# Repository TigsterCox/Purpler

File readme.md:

This is my first keyboard i've ever made
I do NOT reccomend you attempt building it
the current QMK firmware is built for the *BODGED* PCB whereas the KiCad files are for a *FIXED* PCB though it shouldnt be too hard of a fix

Its a 71 Key QWERTY UK ISO build based off of the Durgod Hades 69 ISO
my build uses AKKO Lavender Purple V3's and a generic keycap set from aliex
The RP2040 is a WEACT rpi 2040 as it is also purple (i think you get the theme here)
I use m2x6mm screws that are threaded into plastic, tho you can also adjust it for heatsets and shorter screws (which i plan on doing if i ever do a rebuild)

AGAIN, I DO NOT RECCOMEND BUILDING THIS

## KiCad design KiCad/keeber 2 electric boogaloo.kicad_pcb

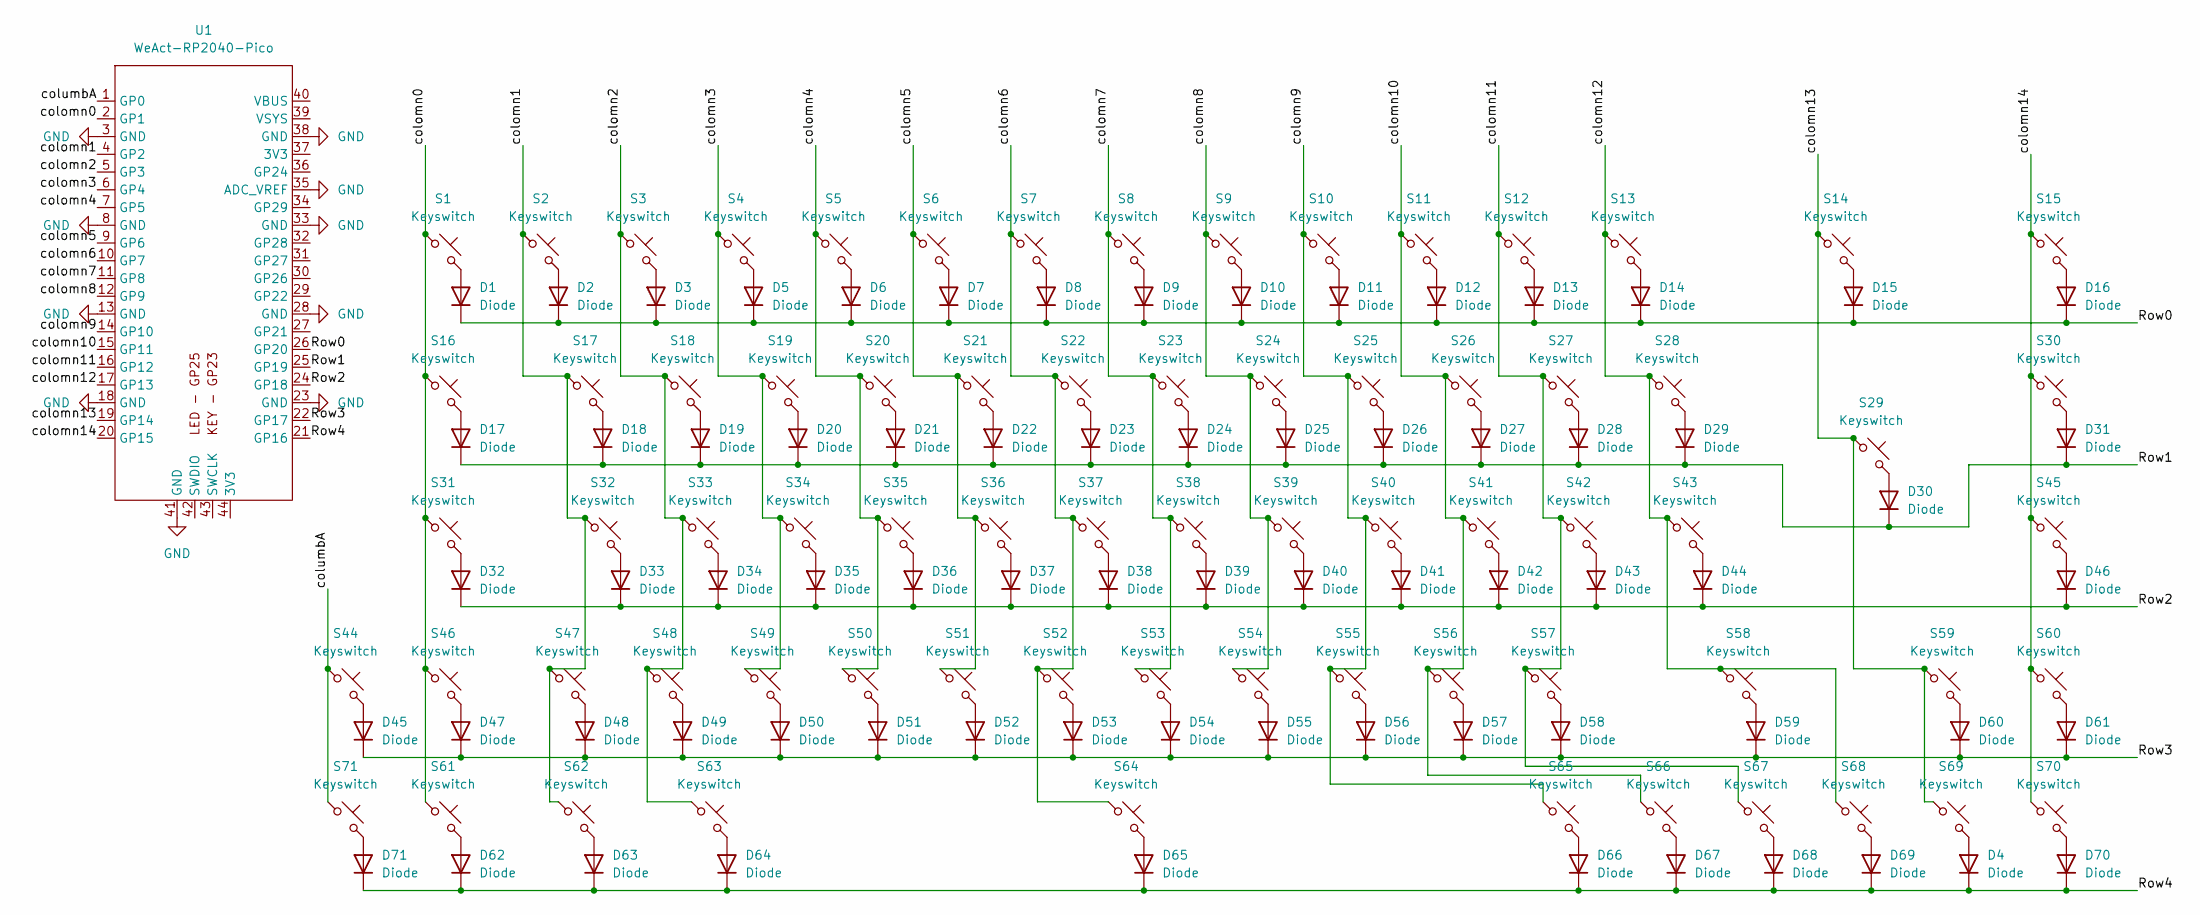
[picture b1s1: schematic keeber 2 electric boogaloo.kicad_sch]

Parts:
D1, D2, D3, D4, D5, D6, D7, D8, D9, D10, D11, D12, D13, D14, D15, D16, D17, D18, D19, D20, D21, D22, D23, D24, D25, D26, D27, D28, D29, D30, D31, D32, D33, D34, D35, D36, D37, D38, D39, D40, D41, D42, D43, D44, D45, D46, D47, D48, D49, D50, D51, D52, D53, D54, D55, D56, D57, D58, D59, D60, D61, D62, D63, D64, D65, D66, D67, D68, D69, D70, D71: Diode; D_SOD-123
S1, S2, S3, S4, S5, S6, S7, S8, S9, S10, S11, S12, S13, S15, S17, S18, S19, S20, S21, S22, S23, S24, S25, S26, S27, S28, S30, S32, S33, S34, S35, S36, S37, S38, S39, S40, S41, S42, S43, S45, S47, S48, S49, S50, S51, S52, S53, S54, S55, S56, S57, S59, S60, S65, S66, S67, S68, S69, S70: Keyswitch; Hotswap_MX_1.00u
S14: Keyswitch; Hotswap_MX_2.00u
S16, S44, S71: Keyswitch; Hotswap_MX_1.50u
S29: Keyswitch; Hotswap_MX_ISOEnter
S31, S58: Keyswitch; Hotswap_MX_1.75u
S46, S61, S62, S63: Keyswitch; Hotswap_MX_1.25u
S64: Keyswitch; Hotswap_MX_6.25u
U1: WeAct-RP2040-Pico

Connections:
/Row0: D1.1 (K), D2.1 (K), D3.1 (K), D5.1 (K), D6.1 (K), D7.1 (K), D8.1 (K), D9.1 (K), D10.1 (K), D11.1 (K), D12.1 (K), D13.1 (K), D14.1 (K), D15.1 (K), D16.1 (K), U1.26 (GP20)
/Row1: D17.1 (K), D18.1 (K), D19.1 (K), D20.1 (K), D21.1 (K), D22.1 (K), D23.1 (K), D24.1 (K), D25.1 (K), D26.1 (K), D27.1 (K), D28.1 (K), D29.1 (K), D30.1 (K), D31.1 (K), U1.25 (GP19)
/Row2: D32.1 (K), D33.1 (K), D34.1 (K), D35.1 (K), D36.1 (K), D37.1 (K), D38.1 (K), D39.1 (K), D40.1 (K), D41.1 (K), D42.1 (K), D43.1 (K), D44.1 (K), D46.1 (K), U1.24 (GP18)
/Row3: D45.1 (K), D47.1 (K), D48.1 (K), D49.1 (K), D50.1 (K), D51.1 (K), D52.1 (K), D53.1 (K), D54.1 (K), D55.1 (K), D56.1 (K), D57.1 (K), D58.1 (K), D59.1 (K), D60.1 (K), D61.1 (K), U1.22 (GP17)
/Row4: D4.1 (K), D62.1 (K), D63.1 (K), D64.1 (K), D65.1 (K), D66.1 (K), D67.1 (K), D68.1 (K), D69.1 (K), D70.1 (K), D71.1 (K), U1.21 (GP16)
/colomn0: S1.1, S16.1, S31.1, S46.1, S61.1, U1.2 (GP1)
/colomn1: S2.1, S17.1, S32.1, S47.1, S62.1, U1.4 (GP2)
/colomn2: S3.1, S18.1, S33.1, S48.1, S63.1, U1.5 (GP3)
/colomn3: S4.1, S19.1, S34.1, S49.1, U1.6 (GP4)
/colomn4: S5.1, S20.1, S35.1, S50.1, U1.7 (GP5)
/colomn5: S6.1, S21.1, S36.1, S51.1, U1.9 (GP6)
/colomn6: S7.1, S22.1, S37.1, S52.1, S64.1, U1.10 (GP7)
/colomn7: S8.1, S23.1, S38.1, S53.1, U1.11 (GP8)
/colomn8: S9.1, S24.1, S39.1, S54.1, U1.12 (GP9)
/colomn9: S10.1, S25.1, S40.1, S55.1, S65.1, U1.14 (GP10)
/colomn10: S11.1, S26.1, S41.1, S56.1, S66.1, U1.15 (GP11)
/colomn11: S12.1, S27.1, S42.1, S57.1, S67.1, U1.16 (GP12)
/colomn12: S13.1, S28.1, S43.1, S58.1, S68.1, U1.17 (GP13)
/colomn13: S14.1, S29.1, S59.1, S69.1, U1.19 (GP14)
/colomn14: S15.1, S30.1, S45.1, S60.1, S70.1, U1.20 (GP15)
/columbA: S44.1, S71.1, U1.1 (GP0)
GND: U1.3 (GND), U1.8 (GND), U1.13 (GND), U1.18 (GND), U1.23 (GND), U1.28 (GND), U1.33 (GND), U1.35 (ADC_VREF), U1.38 (GND), U1.41 (GND)
unnamed: D1.2 (A), S1.2
unnamed: D2.2 (A), S2.2
unnamed: D3.2 (A), S3.2
unnamed: D4.2 (A), S69.2
unnamed: D5.2 (A), S4.2
unnamed: D6.2 (A), S5.2
unnamed: D7.2 (A), S6.2
unnamed: D8.2 (A), S7.2
unnamed: D9.2 (A), S8.2
unnamed: D10.2 (A), S9.2
unnamed: D11.2 (A), S10.2
unnamed: D12.2 (A), S11.2
unnamed: D13.2 (A), S12.2
unnamed: D14.2 (A), S13.2
unnamed: D15.2 (A), S14.2
unnamed: D16.2 (A), S15.2
unnamed: D17.2 (A), S16.2
unnamed: D18.2 (A), S17.2
unnamed: D19.2 (A), S18.2
unnamed: D20.2 (A), S19.2
unnamed: D21.2 (A), S20.2
unnamed: D22.2 (A), S21.2
unnamed: D23.2 (A), S22.2
unnamed: D24.2 (A), S23.2
unnamed: D25.2 (A), S24.2
unnamed: D26.2 (A), S25.2
unnamed: D27.2 (A), S26.2
unnamed: D28.2 (A), S27.2
unnamed: D29.2 (A), S28.2
unnamed: D30.2 (A), S29.2
unnamed: D31.2 (A), S30.2
unnamed: D32.2 (A), S31.2
unnamed: D33.2 (A), S32.2
unnamed: D34.2 (A), S33.2
unnamed: D35.2 (A), S34.2
unnamed: D36.2 (A), S35.2
unnamed: D37.2 (A), S36.2
unnamed: D38.2 (A), S37.2
unnamed: D39.2 (A), S38.2
unnamed: D40.2 (A), S39.2
unnamed: D41.2 (A), S40.2
unnamed: D42.2 (A), S41.2
unnamed: D43.2 (A), S42.2
unnamed: D44.2 (A), S43.2
unnamed: D45.2 (A), S44.2
unnamed: D46.2 (A), S45.2
unnamed: D47.2 (A), S46.2
unnamed: D48.2 (A), S47.2
unnamed: D49.2 (A), S48.2
unnamed: D50.2 (A), S49.2
unnamed: D51.2 (A), S50.2
unnamed: D52.2 (A), S51.2
unnamed: D53.2 (A), S52.2
unnamed: D54.2 (A), S53.2
unnamed: D55.2 (A), S54.2
unnamed: D56.2 (A), S55.2
unnamed: D57.2 (A), S56.2
unnamed: D58.2 (A), S57.2
unnamed: D59.2 (A), S58.2
unnamed: D60.2 (A), S59.2
unnamed: D61.2 (A), S60.2
unnamed: D62.2 (A), S61.2
unnamed: D63.2 (A), S62.2
unnamed: D64.2 (A), S63.2
unnamed: D65.2 (A), S64.2
unnamed: D66.2 (A), S65.2
unnamed: D67.2 (A), S66.2
unnamed: D68.2 (A), S67.2
unnamed: D69.2 (A), S68.2
unnamed: D70.2 (A), S70.2
unnamed: D71.2 (A), S71.2

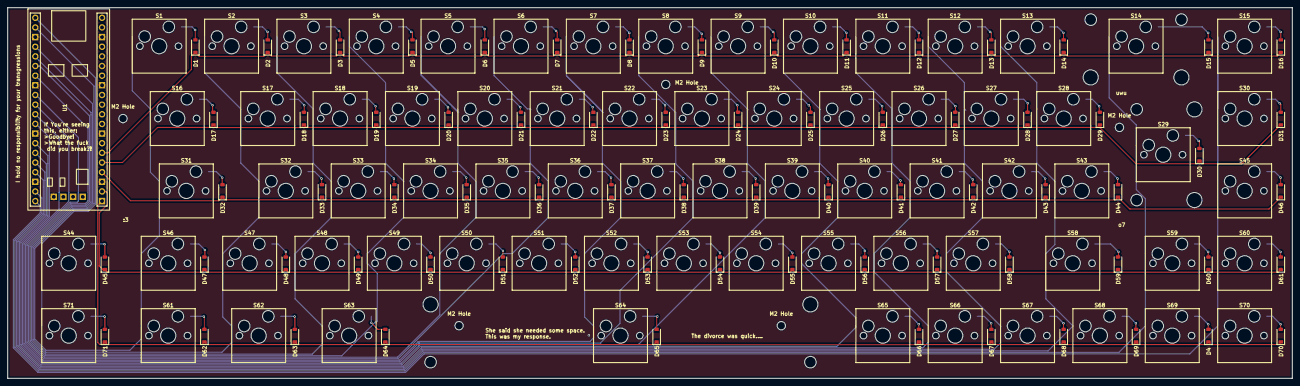
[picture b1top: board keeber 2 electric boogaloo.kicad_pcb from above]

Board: 2 copper layers, 338.2 x 97.6 mm, 148 parts (0 on the bottom side), 93 nets.

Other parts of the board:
M2 Hole, M2 Hole#2, M2 Hole#3, M2 Hole#4, M2 Hole#5: MountingHole_2.2mm_M2

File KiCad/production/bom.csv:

Designator,Footprint,Quantity,Value,LCSC Part #
"D1, D10, D11, D12, D13, D14, D15, D16, D17, D18, D19, D2, D20, D21, D22, D23, D24, D25, D26, D27, D28, D29, D3, D30, D31, D32, D33, D34, D35, D36, D37, D38, D39, D4, D40, D41, D42, D43, D44, D45, D46, D47, D48, D49, D5, D50, D51, D52, D53, D54, D55, D56, D57, D58, D59, D6, D60, D61, D62, D63, D64, D65, D66, D67, D68, D69, D7, D70, D71, D8, D9",D_SOD-123,71,Diode,
"S1, S10, S11, S12, S13, S15, S17, S18, S19, S2, S20, S21, S22, S23, S24, S25, S26, S27, S28, S3, S30, S32, S33, S34, S35, S36, S37, S38, S39, S4, S40, S41, S42, S43, S45, S47, S48, S49, S5, S50, S51, S52, S53, S54, S55, S56, S57, S59, S6, S60, S65, S66, S67, S68, S69, S7, S70, S8, S9",Hotswap_MX_1.00u,59,Keyswitch,
S14,Hotswap_MX_2.00u,1,Keyswitch,
"S16, S44, S71",Hotswap_MX_1.50u,3,Keyswitch,
S29,Hotswap_MX_ISOEnter,1,Keyswitch,
"S31, S58",Hotswap_MX_1.75u,2,Keyswitch,
"S46, S61, S62, S63",Hotswap_MX_1.25u,4,Keyswitch,
S64,Hotswap_MX_6.25u,1,Keyswitch,
U1,WeAct-RP2040-Pico,1,WeAct-RP2040-Pico,

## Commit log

2025-09-16 Init
2025-09-16 shifty shufty
2025-09-16 typo
2025-09-16 cant count
2025-09-16 oops, hit ctrl+s
